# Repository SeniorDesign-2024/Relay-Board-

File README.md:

# Relay-Board
Repo for relay board that controls the charging port connection state

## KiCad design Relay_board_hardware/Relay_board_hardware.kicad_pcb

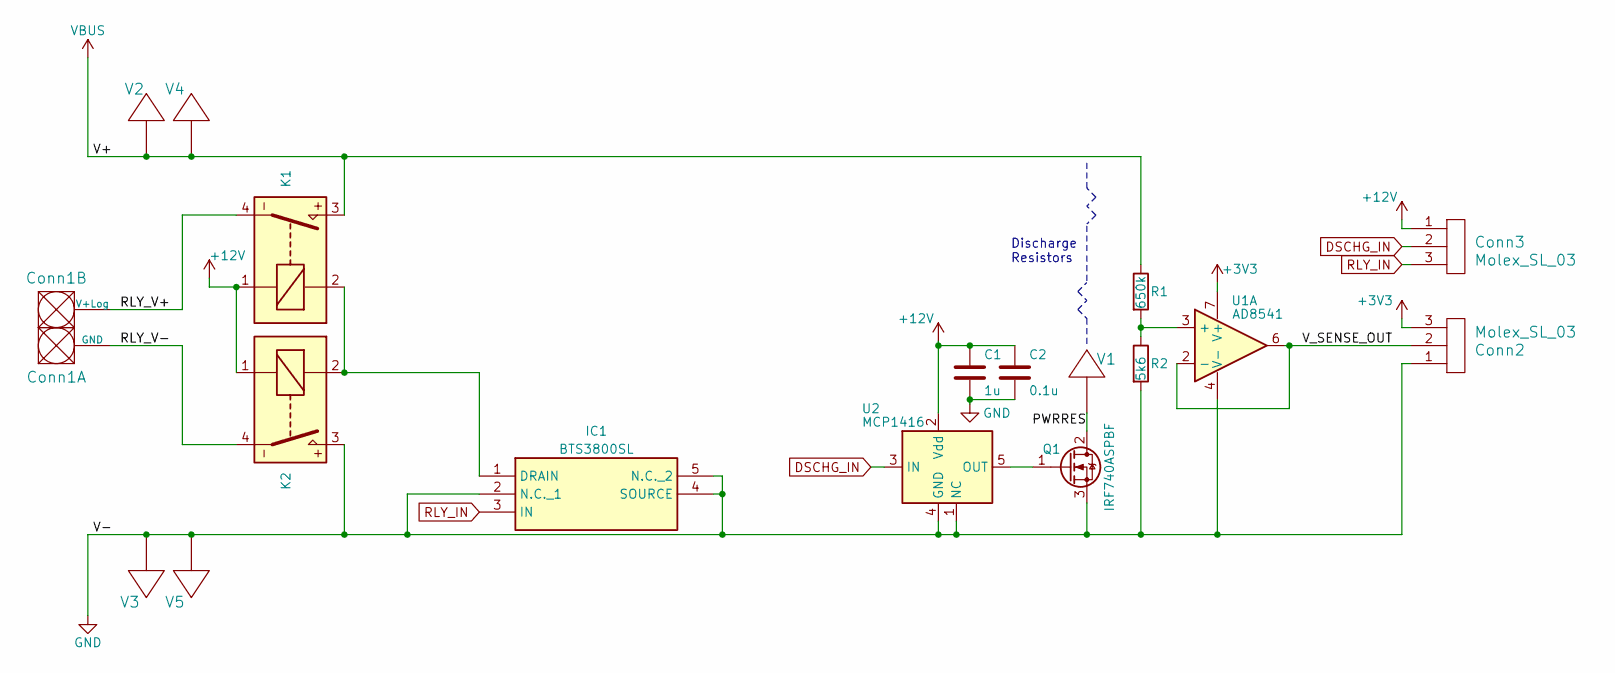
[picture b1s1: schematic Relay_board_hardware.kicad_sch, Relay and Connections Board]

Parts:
C1: 1u; C_0603_1608Metric_Pad1.08x0.95mm_HandSolder
C2: 0.1u; C_0603_1608Metric_Pad1.08x0.95mm_HandSolder
Conn1: AndersonPP; Square_Anderson_2_H_Side_By_Side
Conn2, Conn3: Molex_SL_03; MOLEX_SL_03_Horizontal
IC1: BTS3800SL; Mouser Part Number 726-BTS3800SL
K1, K2: AECN11012
Q1: IRF740ASPBF; TO-263-2
R1: 650k; R_2512_6332Metric_Pad1.40x3.35mm_HandSolder
R2: 5k6; R_2512_6332Metric_Pad1.40x3.35mm_HandSolder
U1: AD8541; SOIC-8_3.9x4.9mm_P1.27mm
U2: MCP1416; SOT-23-5
V1: BATT_PWR_VIA; via_L1000mil_W1000mil
V2, V3, V4, V5: BATT_PWR_VIA; via_L2000mil_W1000mil

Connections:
+3V3: Conn2.3, U1.7 (V+)
+12V: C1.1, C2.1, Conn3.1, K1.1, K2.1, U2.2 (Vdd)
/PWRRES: Q1.2 (D), V1.1
/RLY_V+: Conn1.2 (V+Log), K1.4
/RLY_V-: Conn1.1 (GND), K2.4
/V_SENSE_OUT: Conn2.2, U1.2 (-), U1.6
DSCHG_IN: Conn3.2, U2.3 (IN)
GND: C1.2, C2.2, Conn2.1, IC1.2 (N.C._1), IC1.4 (SOURCE), IC1.5 (N.C._2), K2.3, Q1.3 (S), R2.2, U1.4 (V-), U2.1 (NC), U2.4 (GND), V3.1, V5.1
unnamed: IC1.1 (DRAIN), K1.2, K2.2
unnamed: Q1.1 (G), U2.5 (OUT)
unnamed: R1.2, R2.1, U1.3 (+)
RLY_IN: Conn3.3, IC1.3 (IN)
VBUS: K1.3, R1.1, V2.1, V4.1

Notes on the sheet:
Discharge Resistors

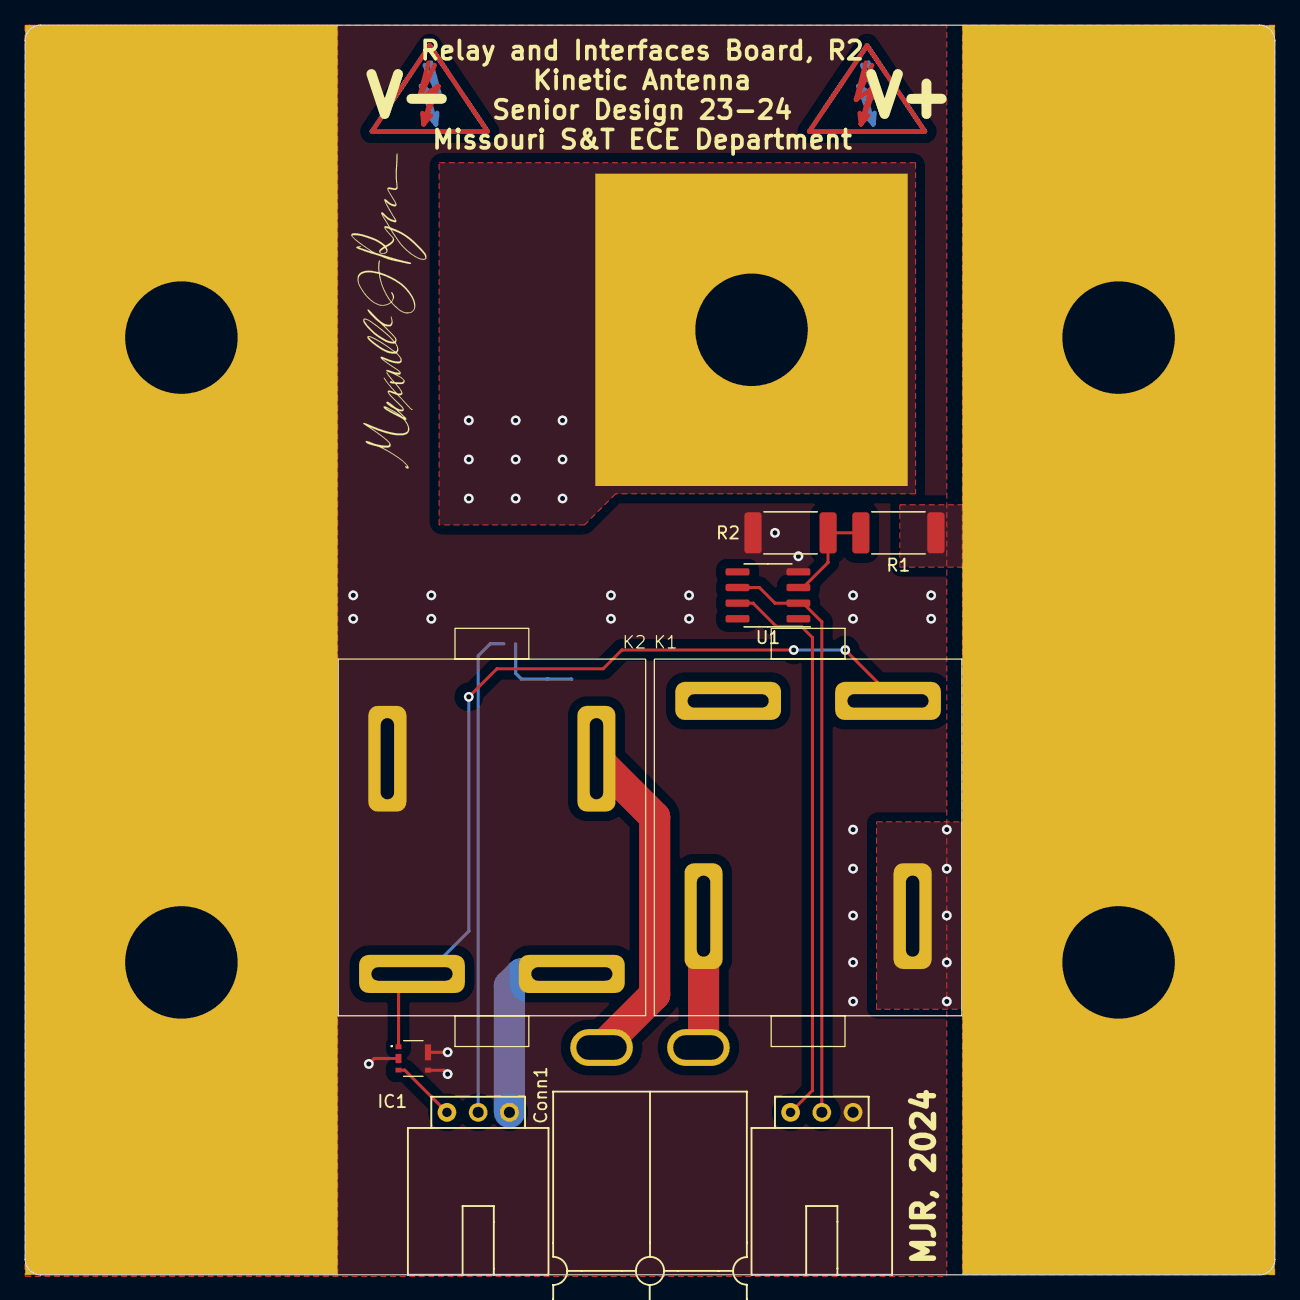
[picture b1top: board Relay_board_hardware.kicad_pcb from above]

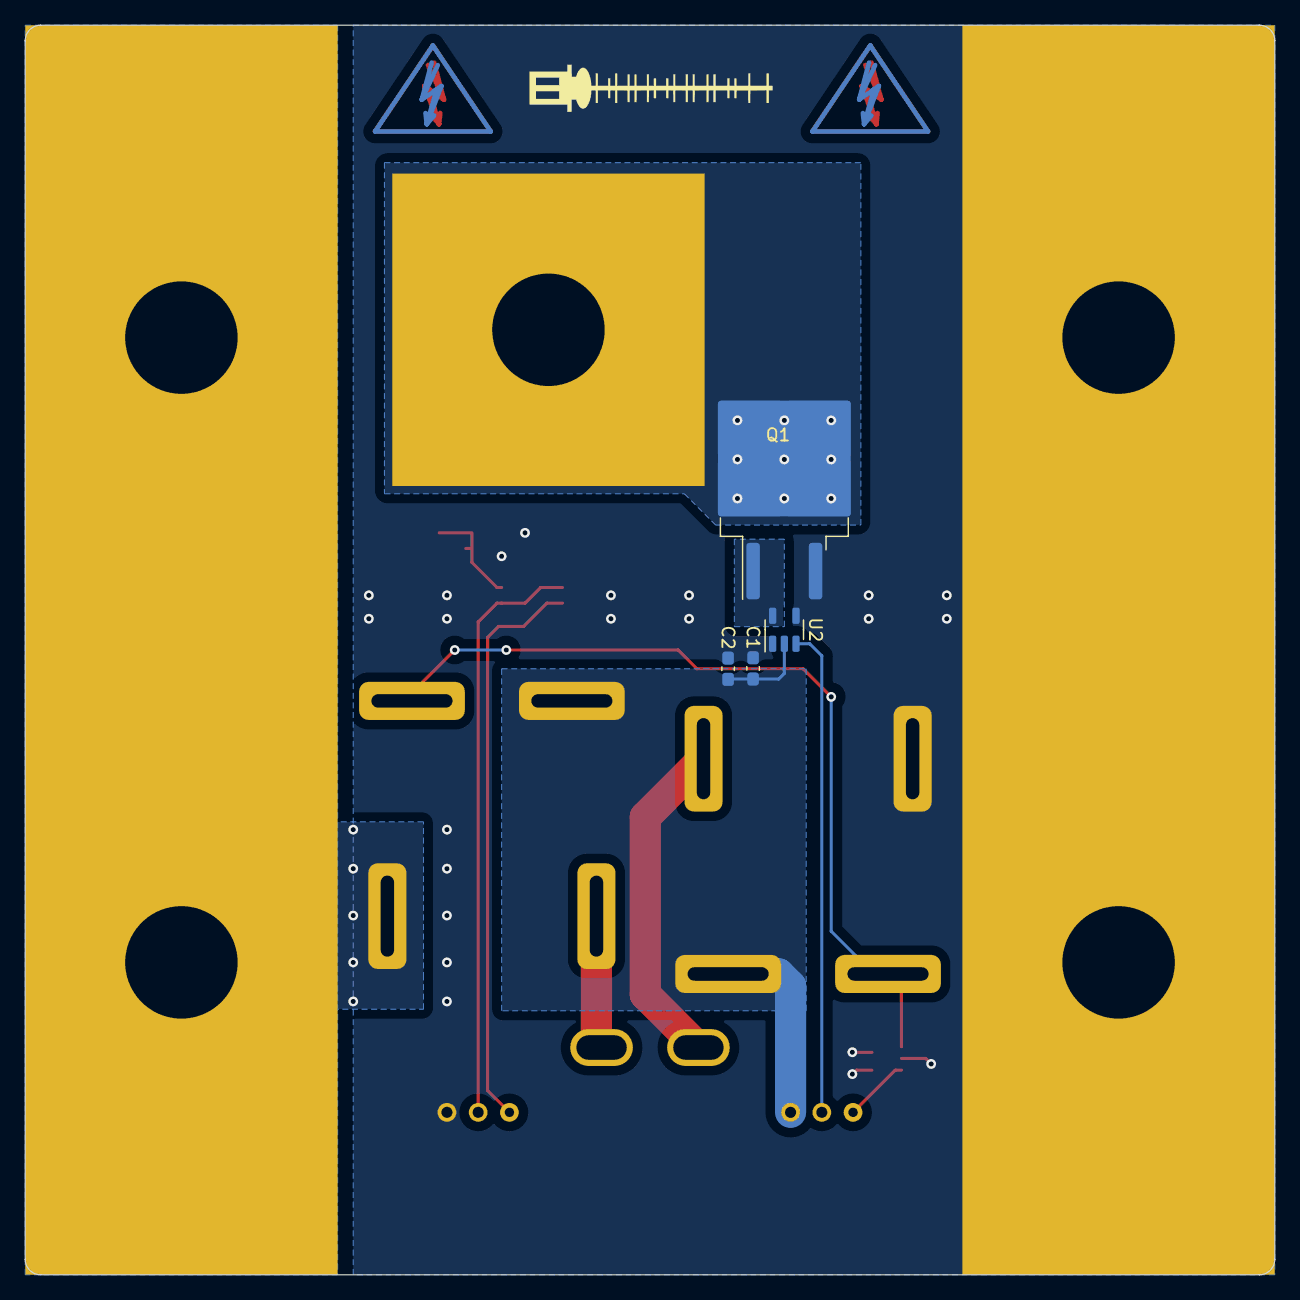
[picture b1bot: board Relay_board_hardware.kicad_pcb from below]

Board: 2 copper layers, 101.6 x 101.6 mm, 18 parts (4 on the bottom side), 13 nets.

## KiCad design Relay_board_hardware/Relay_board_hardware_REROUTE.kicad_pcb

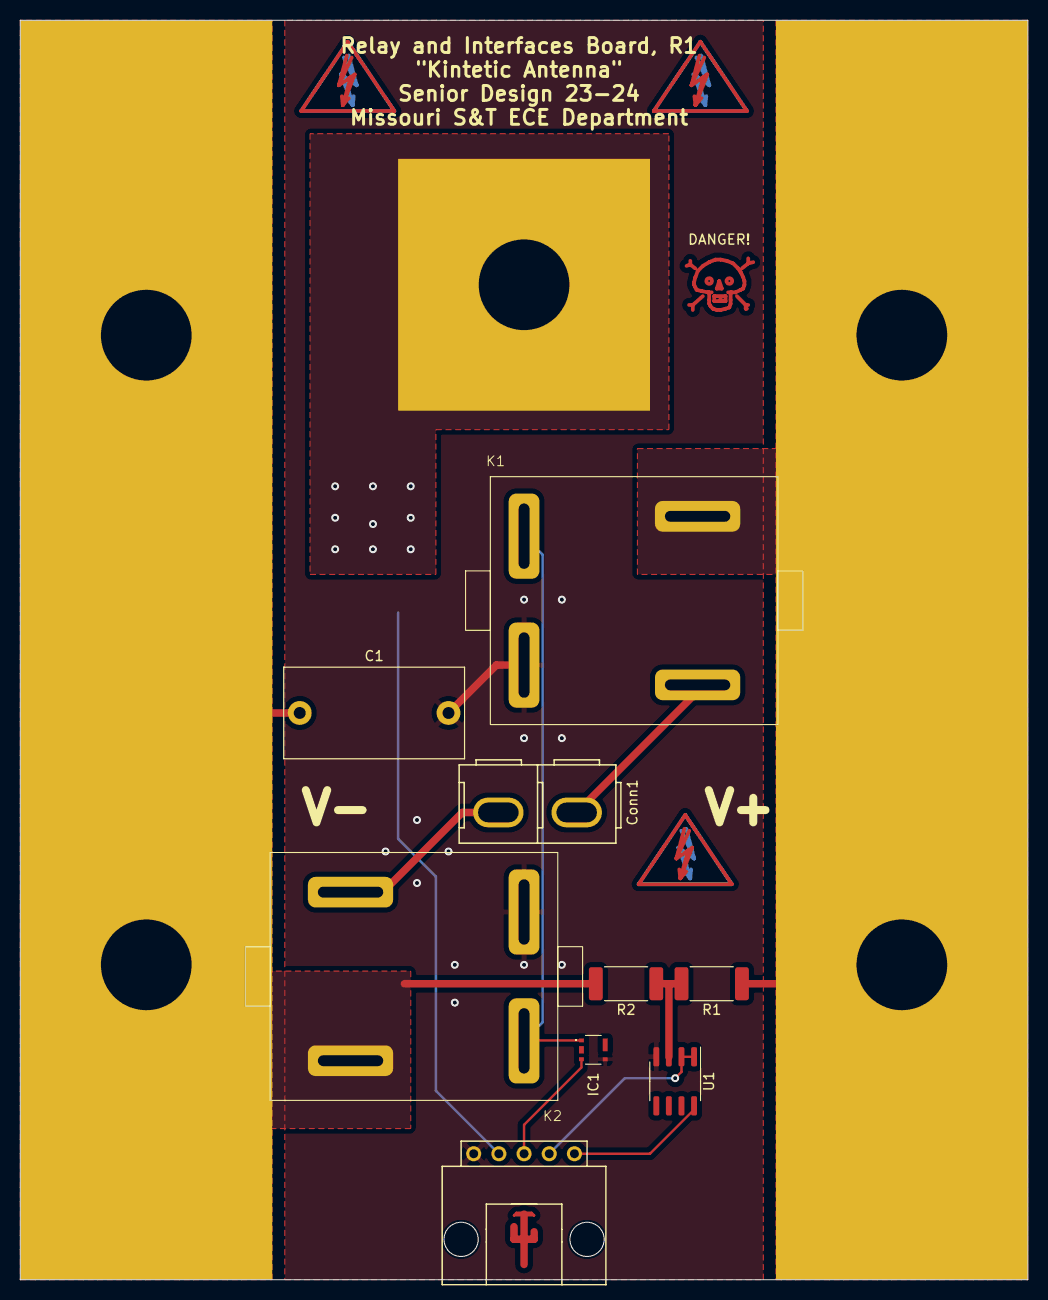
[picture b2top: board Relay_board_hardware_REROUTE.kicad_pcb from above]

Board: 2 copper layers, 101.6 x 127.0 mm, 16 parts (1 on the bottom side), 12 nets.

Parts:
C1: 4.7u; C_Rect_L18.0mm_W9.0mm_P15.00mm_FKS3_FKP3
Conn1: Anderson; Square_Anderson_2_V_Side_By_Side
Conn2: Molex_SL_05; MOLEX_SL_05_Horizontal
DANGER!: Symbol_Danger_CopperTop_Small
IC1: BTS3800SL
K1, K2: AECN11012
Q1: Q_NMOS_GDS; TO-263-2
R1, R2: R; R_2512_6332Metric_Pad1.40x3.35mm_HandSolder
U1: Opamp_Dual; SOIC-8_3.9x4.9mm_P1.27mm
V1: BATT_PWR_VIA; via_L1000mil_W1000mil
V2, V3, V4, V5: BATT_PWR_VIA; via_L2500mil_W1000mil

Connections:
+3V3: Conn2.1, U1.8 (V+)
/PWRRES: Q1.2 (D), V1.1
/RLY_V+: Conn1.1 (VPP), K1.4
/RLY_V-: Conn1.2 (GND), K2.4
/V_SENSE_OUT: Conn2.2, U1.1, U1.2 (-)
DSCHG_IN: Conn2.4, Q1.1 (G)
GND: C1.2, Conn2.5, IC1.4 (SOURCE), K1.1, K2.1, U1.4 (V-)
GNDPWR: C1.1, K2.3, Q1.3 (S), R2.2, V3.1, V5.1
unnamed: IC1.1 (DRAIN), K1.2, K2.2
unnamed: R1.2, R2.1, U1.3 (+)
RLY_IN: Conn2.3, IC1.3 (IN)
VBUS: K1.3, R1.1, V2.1, V4.1

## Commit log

2024-02-18 Rev1 Finished
    Finished a first revision of Relay board
2024-02-19 Cleared design
    Cleared out the layout for max to take over the design
2024-02-21 board R1
    potential changes: anderson placement, IO location, warning correction
2024-02-22 side-by-side-R1
    complete board design with the relays situated side-by-side
2024-02-22 reupload
2024-02-26 board review changes made
    major revisions: curved corners, relocated DSCHG resistor pad, cosmetics. Final dimensions 4x4"
2024-02-26 cosmetic changes
2024-02-27 generated gerbs
2024-02-27 moved trace and generated gerbs
2024-02-27 drill files?
2024-02-27 bom generated
2024-02-27 bom updated with prices
2024-02-27 links are clickable now
2024-02-27 gerbs
2024-03-23 12V connection redesign
2024-03-25 silkscreen updated, relay to rail plane dimensions confirmed, filecleanup,
2024-03-29 R2 edits
    gerbs generated
2024-03-29 added filter cap, changed opamp datasheet
2024-03-29 gerbs, pt2
